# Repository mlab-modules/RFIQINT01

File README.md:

# RFIQINT01B - RF signal I/Q interface

## Parameters

| Parameter | Value | Description |
|-----------|-------|-------------|
| Frequency range | 100 - 1000 MHz |  |
| Interface | RJ45 | CAT 7/A cable is expected |
| Operating and storage temperature | -20 - +30°C |  |
| Operational input voltage for Antenna | 9 - 12 V |  |
| Operational input voltage  | 3.3-3.6 V | 130 mA for LO buffer core |

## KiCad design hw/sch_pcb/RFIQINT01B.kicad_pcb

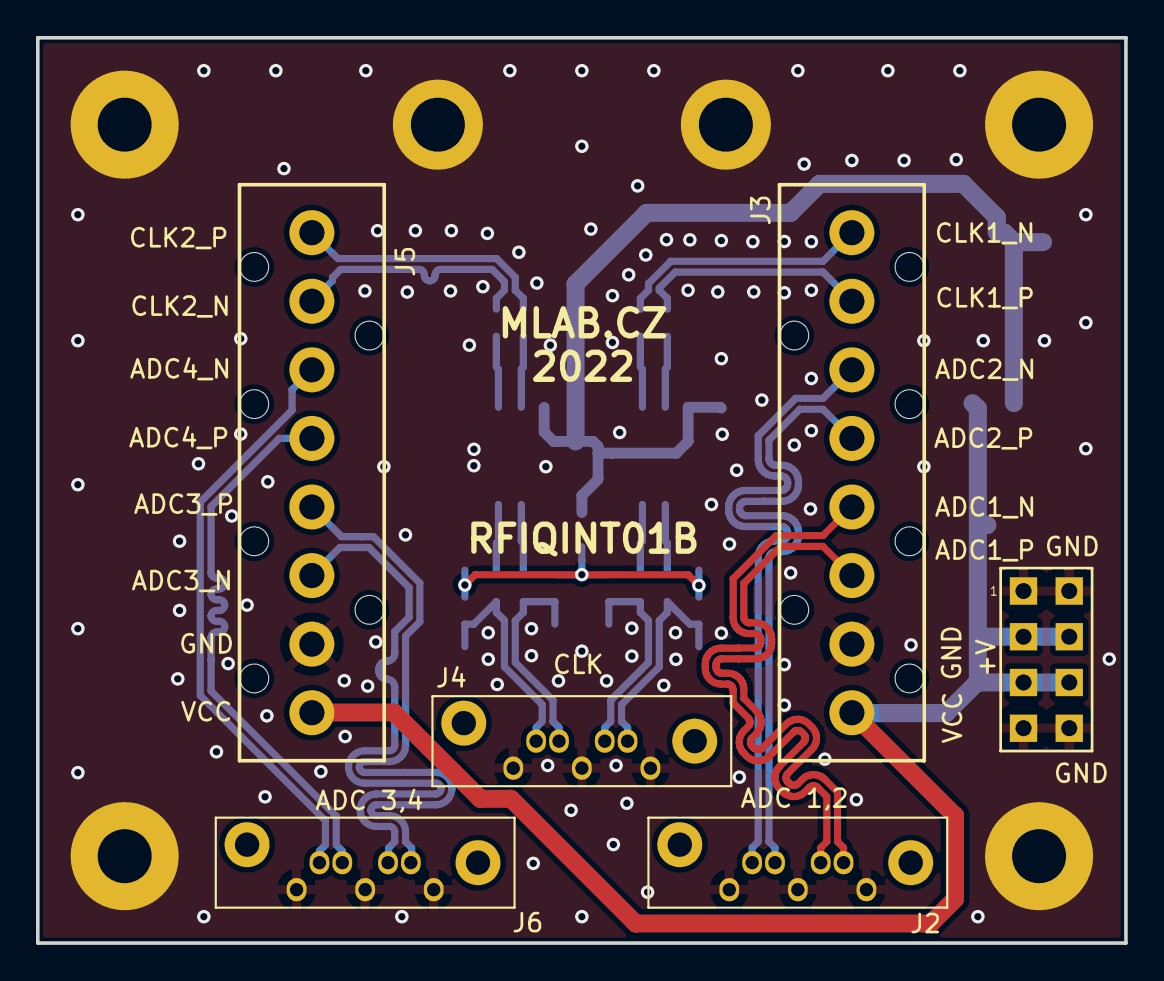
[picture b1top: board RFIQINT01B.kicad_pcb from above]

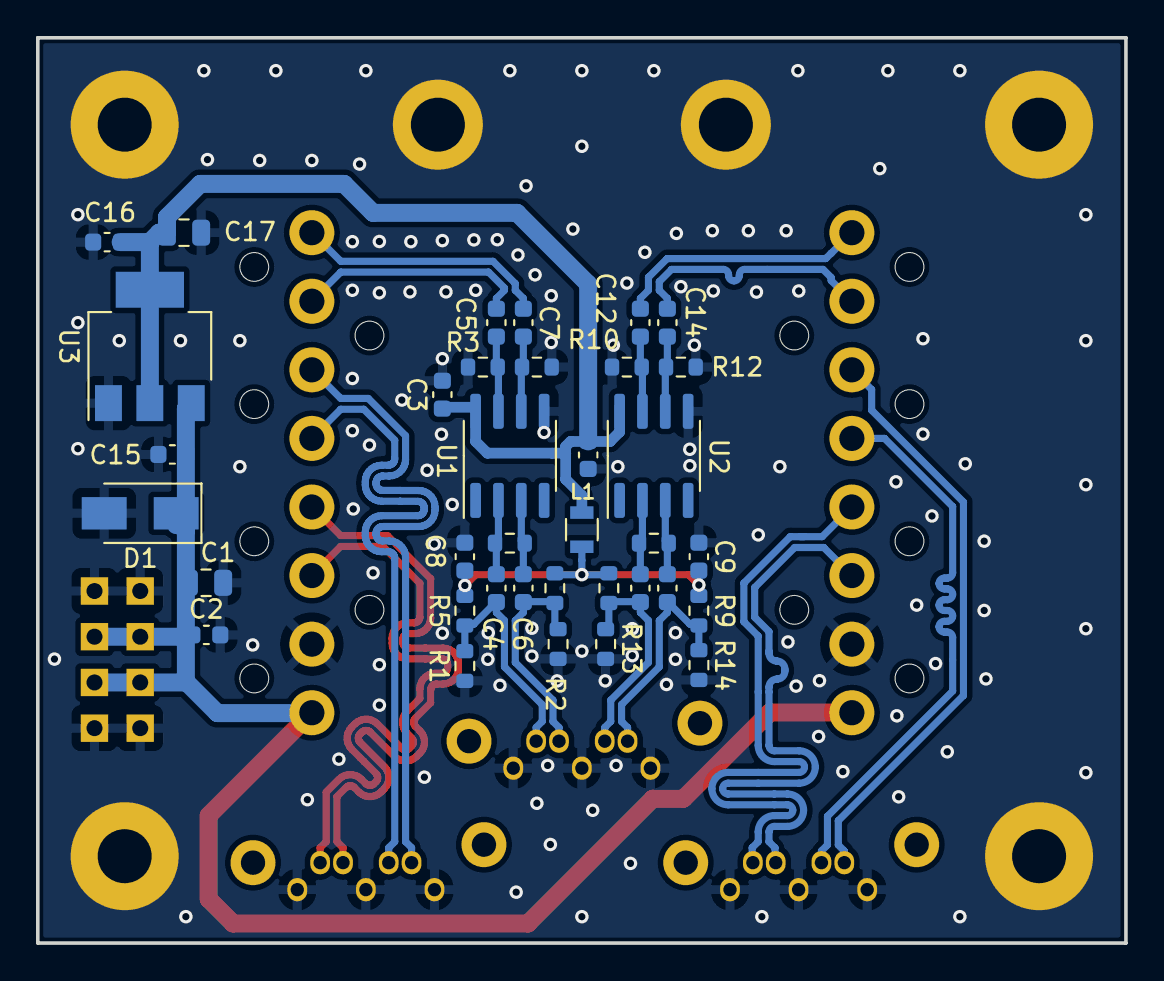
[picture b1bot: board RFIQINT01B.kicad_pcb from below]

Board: 2 copper layers, 60.5 x 50.3 mm, 48 parts (42 on the bottom side), 28 nets.

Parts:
C1, C17: 10uF/16V; C_0805_2012Metric
C2, C3, C4, C5, C6, C7, C8, C9, C10, C11, C12, C13, C14, C15, C16: 100nF; C_0603_1608Metric
D1: M4; D_SMA
J1: HEADER_2x04_PARALLEL; Straight_2x04
J2, J4, J6: SATA7-67491-1030; SATA-7_THT_VERT_2
J3, J5: HEADER_1x08; IDC381-8-110
L1: BLM21PG331SN1D; L_0805
M1, M2, M3, M4, M5, M6: HOLE; MountingHole_3mm
R1, R2, R13, R14: 82; R_0603_1608Metric
R3, R5, R6, R7, R8, R9, R10, R12: 130; R_0603_1608Metric
R4, R11: 100; R_0603_1608Metric
U1, U2: MAX9321; SOIC-8_3.9x4.9mm_P1.27mm
U3: LM1117-3.3; SOT-223-3_TabPin2

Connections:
+3V3: C3.1, C10.1, C16.2, C17.2, L1.2, U1.8 (Vcc), U2.8 (Vcc), U3.2 (VO)
/ADC1_N: J2.3, J3.5
/ADC1_P: J2.2, J3.6
/ADC2_N: J2.6, J3.3
/ADC2_P: J2.5, J3.4
/ADC3_N: J5.3, J6.3
/ADC3_P: J5.4, J6.2
/ADC4_N: J5.6, J6.6
/ADC4_P: J5.5, J6.5
/CLK_IN1_N: C6.2, J4.3, R2.2, R6.1
/CLK_IN1_P: C4.2, J4.2, R1.2, R5.1
/CLK_IN2_N: C13.2, J4.6, R9.2, R14.1
/CLK_IN2_P: C11.2, J4.5, R8.2, R13.1
/CLK_OUT1_N: C7.1, J3.1
/CLK_OUT1_P: C5.1, J3.2
/CLK_OUT2_N: C14.1, J5.7
/CLK_OUT2_P: C12.1, J5.8
GND: C1.2, C2.2, C3.2, C8.1, C9.1, C10.2, C15.1, C16.1, C17.1, D1.2 (A), J1.1, J1.2, J1.7, J1.8, J2.1, J2.4, J2.7, J3.7, J4.1, J4.4, J4.7, J5.2, J6.1, J6.4, J6.7, M1.1, M2.1, M3.1, M4.1, M5.1, M6.1, R1.1, R2.1, R3.1, R7.2, R10.1, R12.2, R13.2, R14.2, U1.5 (Vee), U2.5 (Vee), U3.1 (GND)
unnamed: C4.1, R4.1, U1.2 (D)
unnamed: C5.2, R3.2, U1.7 (Q)
unnamed: C6.1, R4.2, U1.3 (D')
unnamed: C7.2, R7.1, U1.6 (Q')
unnamed: C8.2, C9.2, L1.1, R5.2, R6.2, R8.1, R9.1
unnamed: C11.1, R11.1, U2.2 (D)
unnamed: C12.2, R10.2, U2.7 (Q)
unnamed: C13.1, R11.2, U2.3 (D')
unnamed: C14.2, R12.1, U2.6 (Q')
VCC: C1.1, C2.1, C15.2, D1.1 (K), J1.3, J1.4, J1.5, J1.6, J3.8, J5.1, U3.3 (VI)

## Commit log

2020-06-15 Initial design.
2020-10-28 Fix license.
2022-03-08 Ulozeni v novem formatu KiCAD. A smazani starych dat.
2022-03-08 Prejmenovani kicad projektu
2022-03-08 Edit. #3 #2
2022-03-09 Update title block. Adding link to the datasheet.
2022-03-10 Fix differential pair routing #3.
2022-05-06 Add actions settings
2022-05-06 Update doc/assets
2022-05-06 Edit PCB
2022-05-11 Update actions products
2022-05-25 Editace podkladu pro osazovani
2023-05-25 automated commit; add github actions
2023-05-25 Update metadata files
2023-05-28 Update workflow files
2023-07-05 automated commit; rename source files to new naming convence
2023-09-16 Update image to image_title
2023-09-16 Update status
